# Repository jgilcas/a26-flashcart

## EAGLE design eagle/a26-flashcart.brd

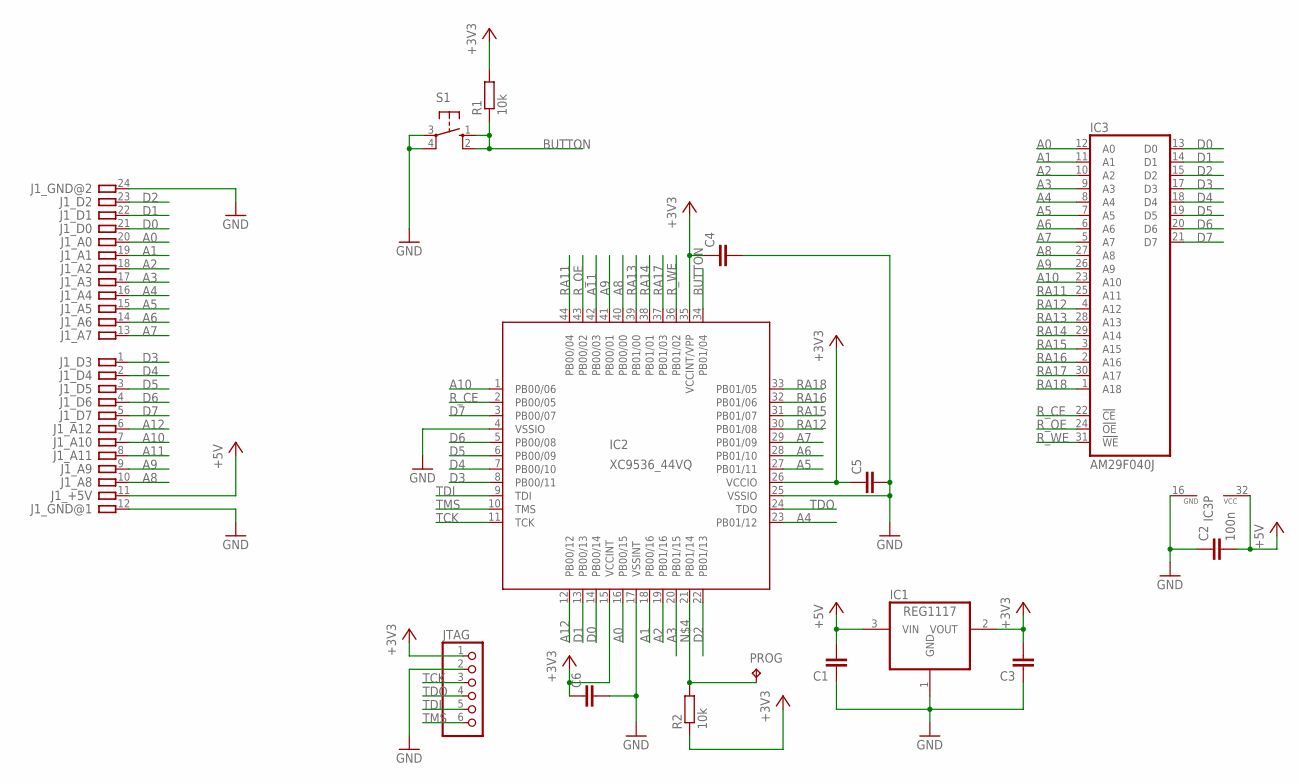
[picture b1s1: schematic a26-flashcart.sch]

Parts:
C1, C3, C4, C5, C6: C-EUC0603; C0603
C2: 100n; C0603
IC1: REG1117; SOT223
IC2: XC9536_44VQ; SQFP-S-10X10-44
IC3: AM29F040J; PLCC32R
J1: ATARI-2600-SMALL
JTAG: PINHD-1X6; 1X06
PROG: TPTP15R; TP15R
R1, R2: 10k; R0603
S1: 10-XX; B3F-10XX

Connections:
+3V3: C3.2, C4.1, C5.1, C6.1, IC1.2 (VOUT), IC2.15 (VCCINT), IC2.26 (VCCIO), IC2.35 (VCCINT/VPP), JTAG.1, R1.2, R2.1
+5V: C1.2, C2.2, IC1.3 (VIN), IC3.32 (VCC), J1.11
A0: IC2.16 (PB00/15), IC3.12 (A0), J1.20
A1: IC2.18 (PB00/16), IC3.11 (A1), J1.19
A2: IC2.19 (PB01/16), IC3.10 (A2), J1.18
A3: IC2.20 (PB01/15), IC3.9 (A3), J1.17
A4: IC2.23 (PB01/12), IC3.8 (A4), J1.16
A5: IC2.27 (PB01/11), IC3.7 (A5), J1.15
A6: IC2.28 (PB01/10), IC3.6 (A6), J1.14
A7: IC2.29 (PB01/09), IC3.5 (A7), J1.13
A8: IC2.40 (PB00/00), IC3.27 (A8), J1.10
A9: IC2.41 (PB00/01), IC3.26 (A9), J1.9
A10: IC2.1 (PB00/06), IC3.23 (A10), J1.7
A11: IC2.42 (PB00/03), J1.8
A12: IC2.12 (PB00/12), J1.6
BUTTON: IC2.34 (PB01/04), R1.1, S1.1 (S), S1.2 (S1)
D0: IC2.14 (PB00/14), IC3.13 (D0), J1.21
D1: IC2.13 (PB00/13), IC3.14 (D1), J1.22
D2: IC2.22 (PB01/13), IC3.15 (D2), J1.23
D3: IC2.8 (PB00/11), IC3.17 (D3), J1.1
D4: IC2.7 (PB00/10), IC3.18 (D4), J1.2
D5: IC2.6 (PB00/09), IC3.19 (D5), J1.3
D6: IC2.5 (PB00/08), IC3.20 (D6), J1.4
D7: IC2.3 (PB00/07), IC3.21 (D7), J1.5
GND: C1.1, C2.1, C3.1, C4.2, C5.2, C6.2, IC1.1 (GND), IC2.4 (VSSIO), IC2.17 (VSSINT), IC2.25 (VSSIO), IC3.16 (GND), J1.12, J1.24, JTAG.2, S1.3, S1.4 (P1)
unnamed: IC2.21 (PB01/14), PROG.TP, R2.2
RA11: IC2.44 (PB00/04), IC3.25 (A11)
RA12: IC2.30 (PB01/08), IC3.4 (A12)
RA13: IC2.39 (PB01/00), IC3.28 (A13)
RA14: IC2.38 (PB01/01), IC3.29 (A14)
RA15: IC2.31 (PB01/07), IC3.3 (A15)
RA16: IC2.32 (PB01/06), IC3.2 (A16)
RA17: IC2.37 (PB01/03), IC3.30 (A17)
RA18: IC2.33 (PB01/05), IC3.1 (A18)
R_CE: IC2.2 (PB00/05), IC3.22 (!CE)
R_OE: IC2.43 (PB00/02), IC3.24 (!OE)
R_WE: IC2.36 (PB01/02), IC3.31 (!WE)
TCK: IC2.11 (TCK), JTAG.3
TDI: IC2.9 (TDI), JTAG.5
TDO: IC2.24 (TDO), JTAG.4
TMS: IC2.10 (TMS), JTAG.6

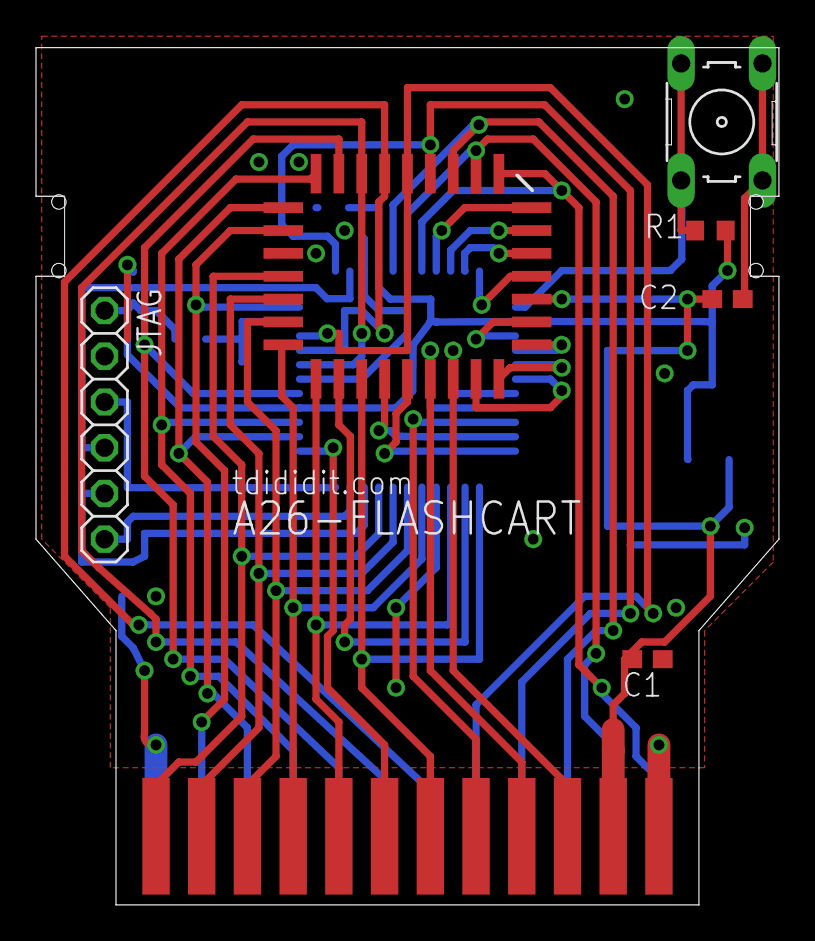
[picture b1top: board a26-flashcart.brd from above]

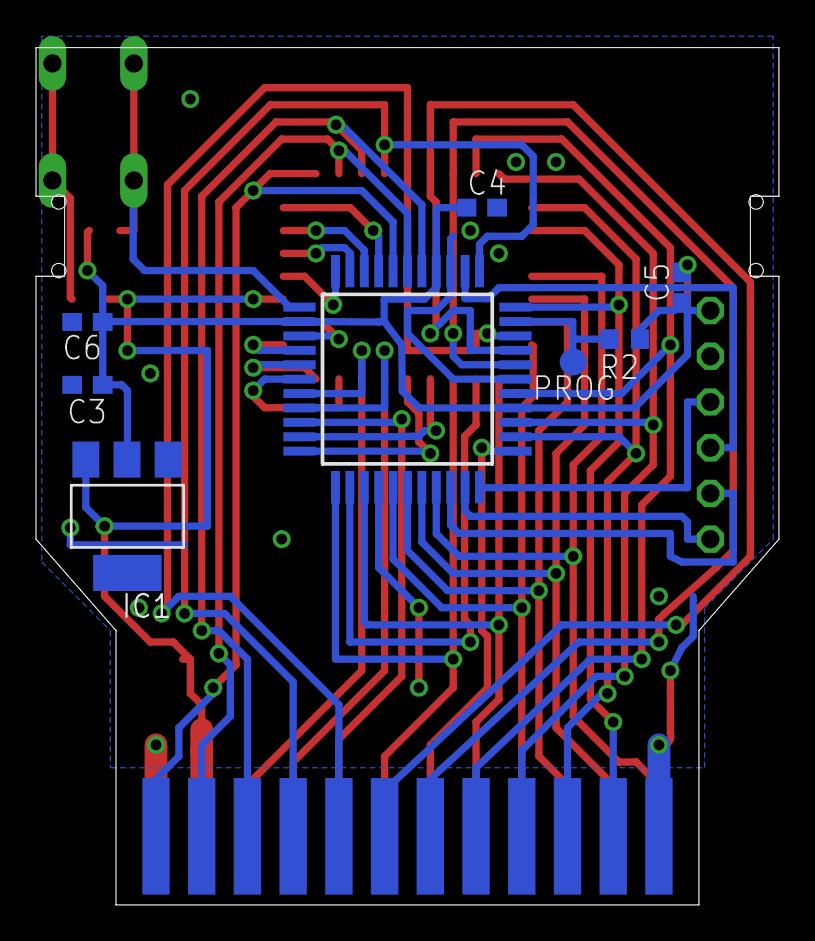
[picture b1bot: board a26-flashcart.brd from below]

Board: 2 copper layers, 41.3 x 47.6 mm, 15 parts (8 on the bottom side), 41 nets.

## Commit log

2016-03-03 :space_invader: Added .gitattributes
2016-03-11 hardware production files
2016-03-11 rom picker source code
